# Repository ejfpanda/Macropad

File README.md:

# Lily-Pad

## Note: I didn't understand how to use github until today so things probably aren't laid out properly.

It has 6 keys -> 5 switches + 1 rotary encoder switch , a rotary encoder, an OLED display and 2 SK6812 MINI - E LEDs. It uses kmk firmware and circuit python.

## PCB:

## CAD Case:

## Firmware:

I used kmk firmware and circuit python.

I have two layers: base layer 0 and layer 1.

On base the keys are copy, paste, save, undo, mute and hold key 6 for layer 1.

While key 6 is held keys are play/pause, next, previous and a macro string saying 'sent from my Lily-Pad'

The encoder in layer 0 is volume up and down (clockwise and counter) and in layer 1 is brightness up and down.

The OLED display shows title, current layer and also it shows last key pressed.

The LEDs flash briefly when you press a key.

## Required parts:

| Component | Amount |
| :--- | :---: |
| **Seeed XIAO RP2040** | 1x |
| **MX-Style switches** | 5x |
| **1N4148 Diodes** | 6x | 
| **EC11 Rotary encoder** | 1x |
| **0.91 inch OLED display** | 1x |
| **DSA keycaps** | 5x |
| **SK6812 MINI-E LED** | 2x |
| **M3x16mm screw** | 4x |
| **Case** (2 printed parts) | 1x |
| **PCB** | 1x |

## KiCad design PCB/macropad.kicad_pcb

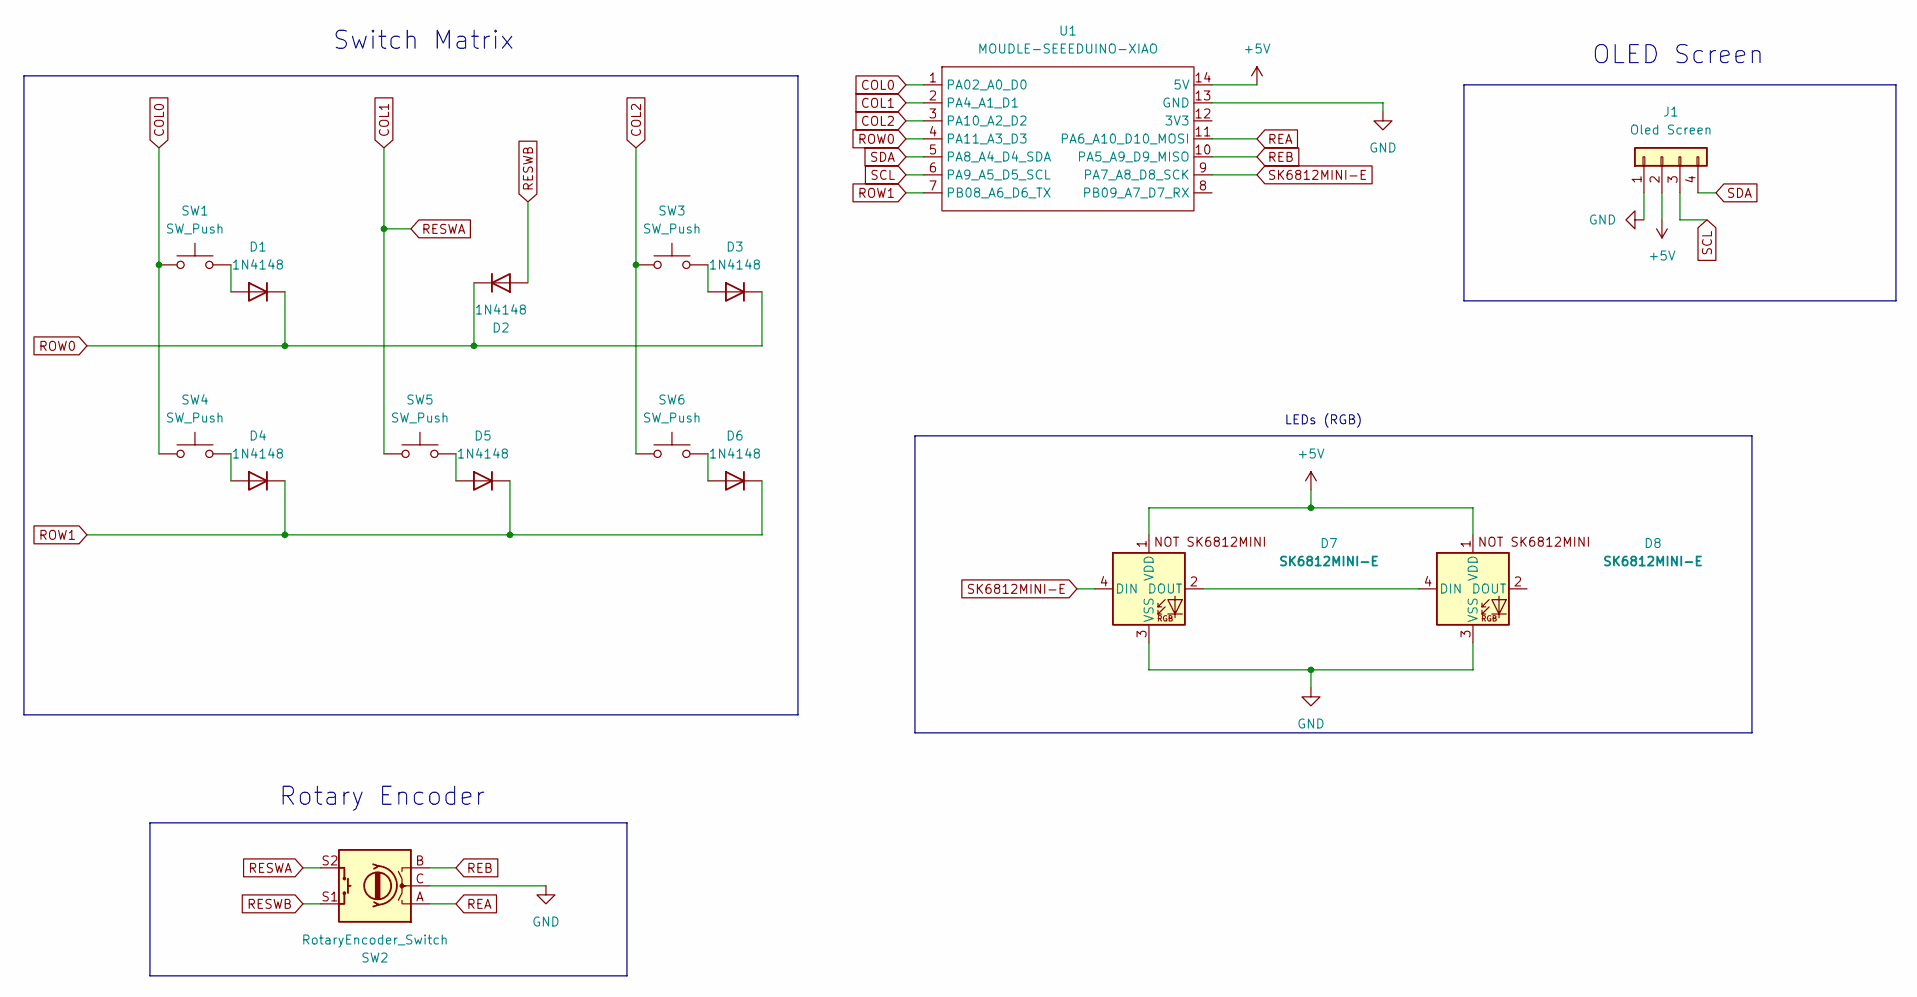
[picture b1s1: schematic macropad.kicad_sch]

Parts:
D1, D2, D3, D4, D5, D6: 1N4148; D_DO-35_SOD27_P7.62mm_Horizontal
D7, D8: SK6812MINI-E; SK6812MINI-E_fixed
J1: Oled Screen; PinHeader_1x04_P2.54mm_Vertical
SW1, SW3, SW4, SW5, SW6: SW_Push; SW_Cherry_MX_1.00u_PCB
SW2: RotaryEncoder_Switch; RotaryEncoder_Alps_EC11E-Switch_Vertical_H20mm
U1: MOUDLE-SEEEDUINO-XIAO; XIAO-Generic-Hybrid-14P-2.54-21X17.8MM

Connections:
+5V: D7.1 (VDD), D8.1 (VDD), J1.2, U1.14 (5V)
COL0: SW1.1, SW4.1, U1.1 (PA02_A0_D0)
COL1: SW2.S2, SW5.1, U1.2 (PA4_A1_D1)
COL2: SW3.1, SW6.1, U1.3 (PA10_A2_D2)
GND: D7.3 (VSS), D8.3 (VSS), J1.1, SW2.C, U1.13 (GND)
unnamed: D1.2 (A), SW1.2
unnamed: D3.2 (A), SW3.2
unnamed: D4.2 (A), SW4.2
unnamed: D5.2 (A), SW5.2
unnamed: D6.2 (A), SW6.2
unnamed: D7.2 (DOUT), D8.4 (DIN)
REA: SW2.A, U1.11 (PA6_A10_D10_MOSI)
REB: SW2.B, U1.10 (PA5_A9_D9_MISO)
RESWB: D2.2 (A), SW2.S1
ROW0: D1.1 (K), D2.1 (K), D3.1 (K), U1.4 (PA11_A3_D3)
ROW1: D4.1 (K), D5.1 (K), D6.1 (K), U1.7 (PB08_A6_D6_TX)
SCL: J1.3, U1.6 (PA9_A5_D5_SCL)
SDA: J1.4, U1.5 (PA8_A4_D4_SDA)
SK6812MINI-E: D7.4 (DIN), U1.9 (PA7_A8_D8_SCK)

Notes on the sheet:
OLED Screen
Rotary Encoder
LEDs (RGB)
Switch Matrix

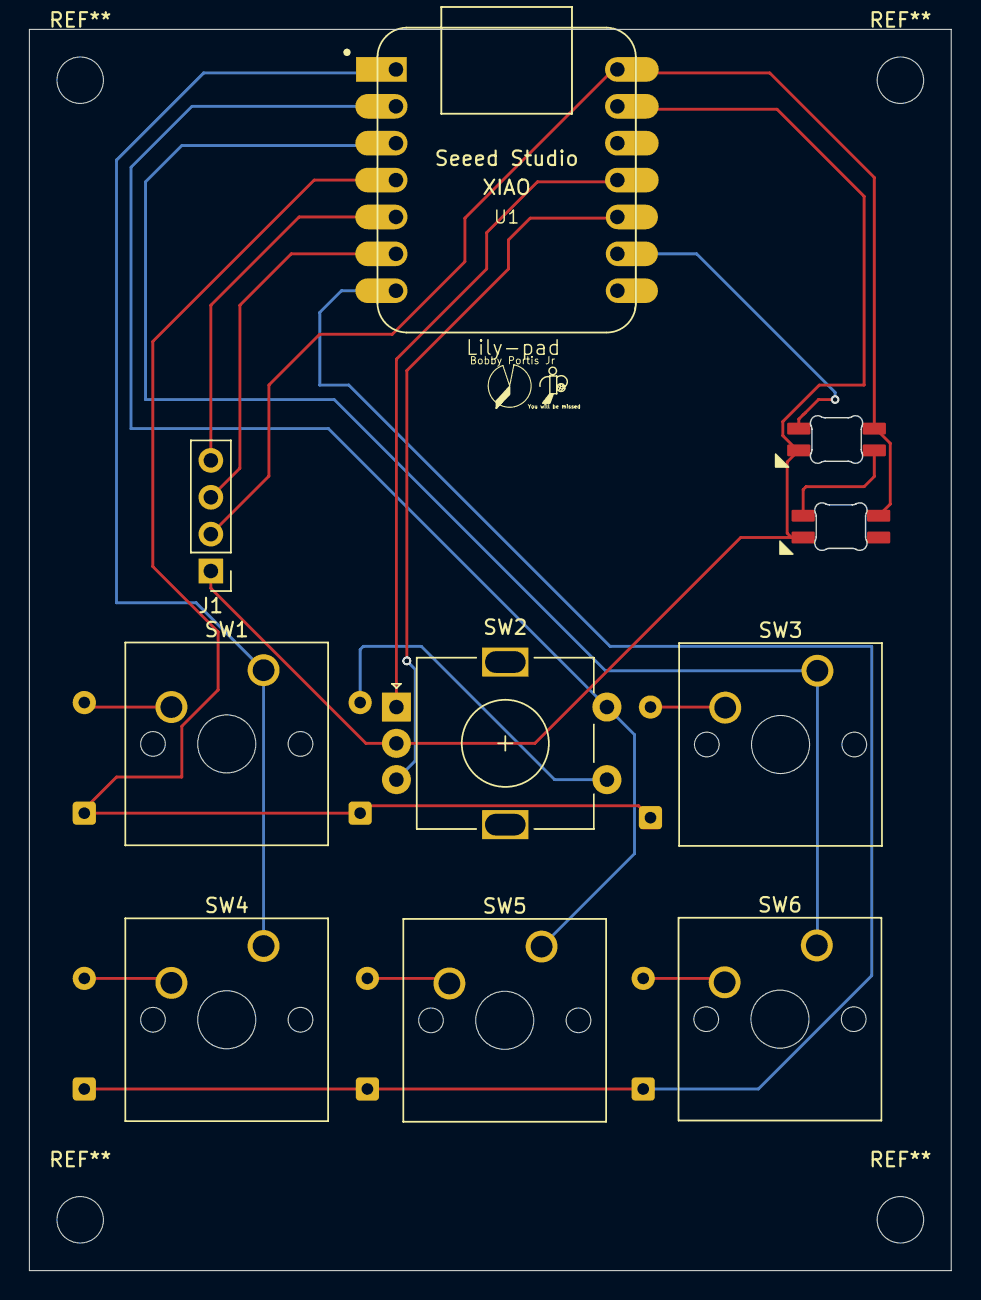
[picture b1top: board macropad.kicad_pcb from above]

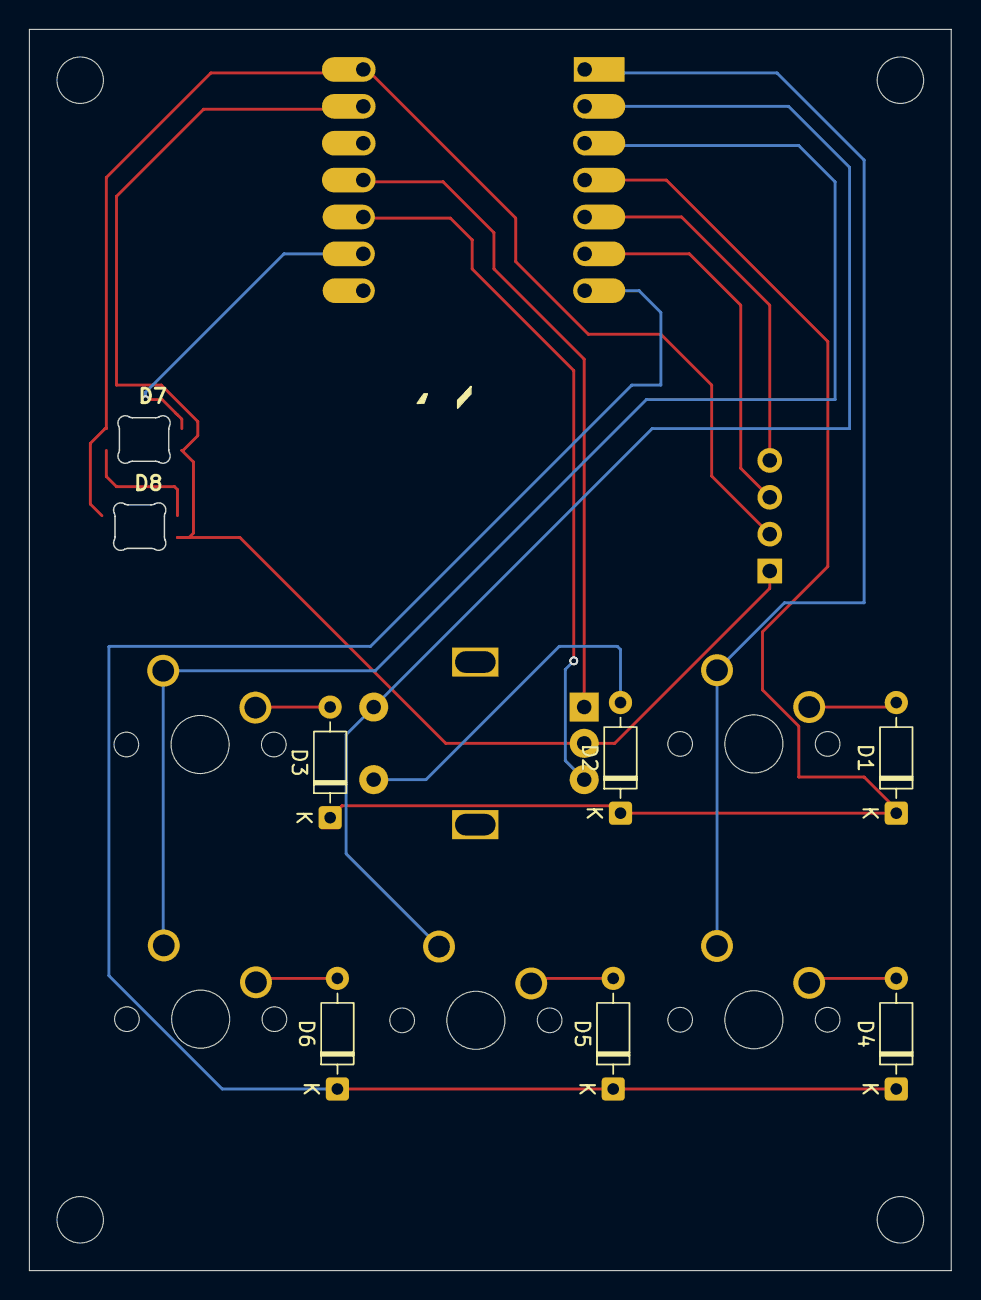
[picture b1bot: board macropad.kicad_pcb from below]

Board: 2 copper layers, 63.5 x 85.5 mm, 16 parts (8 on the bottom side), 19 nets.
